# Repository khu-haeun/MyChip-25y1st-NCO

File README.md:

# My Chip Service 25y1st: **12-bit CORDIC-based NCO**

## Notice: What is **My Chip Service**?
An initiative in South Korea that provides MPW (Multi-Project Wafer) services using public fabrication facilities (fabs) for undergraduate and graduate students.
* **Official Website:** [https://www.moafab.kr](https://www.moafab.kr/css/myPage/bussiness/myChip/info)
* **Design Kit (Open-Source):** [ETRI 0.5um CMOS MPW Standard Cell DK](https://github.com/GoodKook/ETRI-0.5um-CMOS-MPW-Std-Cell-DK/tree/main)

---

## Project: 12-bit CORDIC-based NCO

### 1. Overview

*Fig 1. System Architecture*

*Fig 2. NCO implemented on a PCB using 'My Chip'*

* **Description:** A **Numerically Controlled Oscillator (NCO)** is a digital circuit that generates synchronous, discrete-time, discrete-valued representations of sinusoidal waveforms. This project implements an NCO using a **CORDIC (Coordinate Rotation Digital Computer)** array processor to calculate trigonometric values. The complete verification environment and system structure are illustrated in **Fig 1**.

* **Key Challenges: Overcoming Physical Constraints**
    * **Core Limits:** Since the NCO design exceeded the single-chip area limit, it was **partitioned into three sub-circuits** as shown in **Fig 2**:
        1. **Phase Accumulator:** Generates the phase angle.
        2. **CORDIC Processing Element:** Performs the vector rotation.
        3. **Output Terminal:** Manages the final data output, including quadrant restoration.
    * **Pad Limits:** Each chip is limited to **28 pins**. the I/O for each sub-circuit was implemented using a **2-bit serial interface**.

---

### 2. Directory Structure
```text
├── 0_Algorithm (Algorithm development, including output plots and verification)
│   ├── c_untimed: C-based NCO algorithm
│   ├── cpp_untimed: C++ based NCO algorithm
│   └── sc_timed: SystemC-based NCO model (Clock-event-based cycle-accurate design)
|
├── 1_Parallel_IO (Reference design using parallel I/O (Not implemented in this version))
|
├── 2_Splited_IO (RTL-to-GDS with Open-Source Design Kit, including output plots and verification)
│   ├── 2_0_Top_NCO: Integrated NCO system comprising all three sub-circuits
│   ├── 2_1_Phase_Acc: Sub-circuit 1
│   ├── 2_2_Cordic_Element: Sub-circuit 2
│   ├── 2_3_Output_Terminal: Sub-circuit 3
|
└── 3_Application (application cases)
    ├── 3_0_Generate_Sinusoid: Sinusoidal waveform generation
    ├── 3_1_QPSK_Communication_prototype: QPSK simulation for the prototype board
    └── 3_2_QPSK_Communication_pcb: QPSK simulation for the final PCB

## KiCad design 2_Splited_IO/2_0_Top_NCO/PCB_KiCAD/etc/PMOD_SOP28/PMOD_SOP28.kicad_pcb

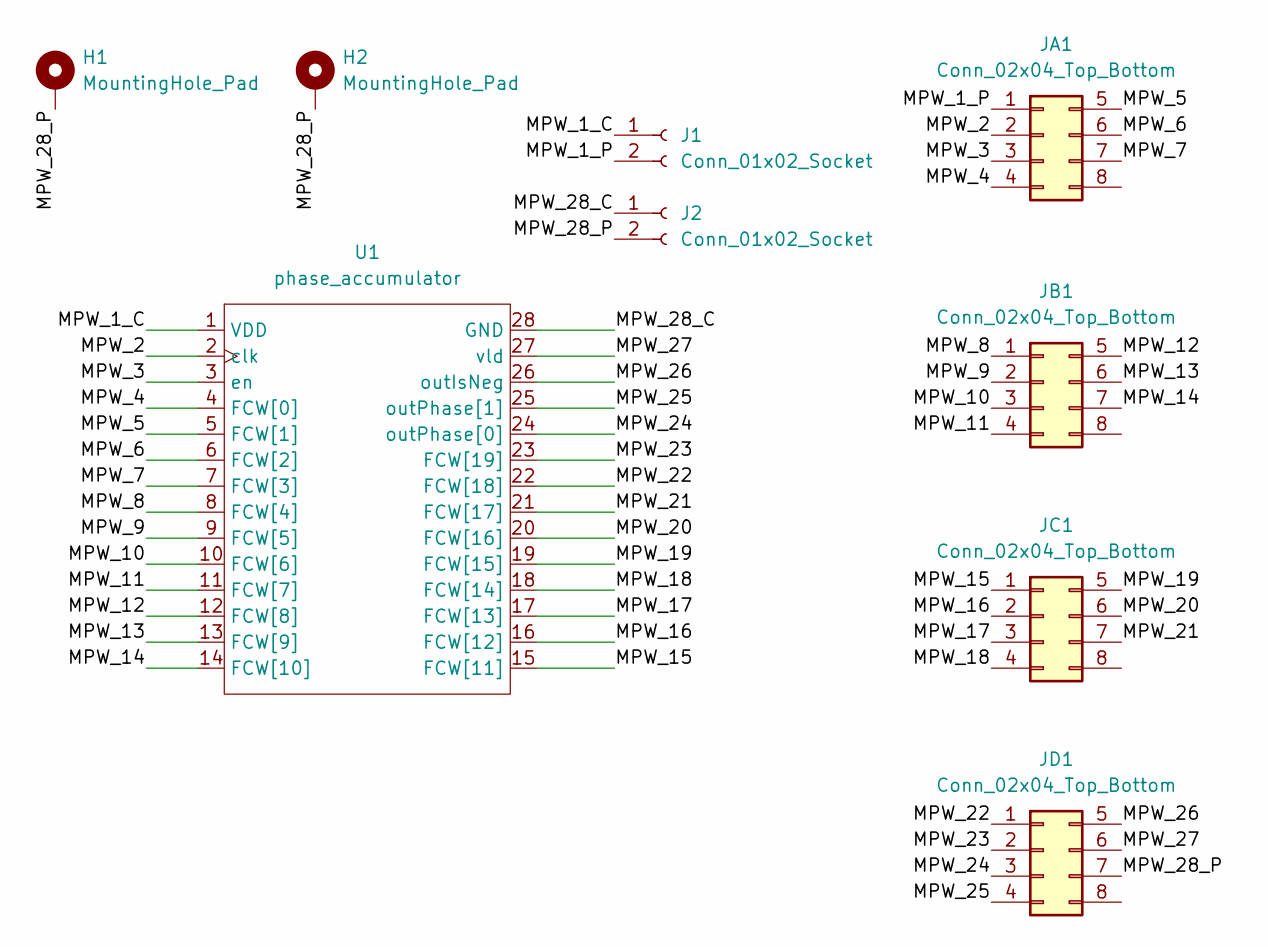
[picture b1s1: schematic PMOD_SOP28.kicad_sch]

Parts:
H1, H2: MountingHole_Pad; MountingHole_3.2mm_M3_Pad
J1, J2: Conn_01x02_Socket; PinHeader_1x02_P2.54mm_Vertical
JA1: Conn_02x04_Top_Bottom; PinSocket_2x04_P2.54mm_Vertical
JB1: Conn_02x04_Top_Bottom; PinSocket_2x04_P2.54mm_Vertical
JC1: Conn_02x04_Top_Bottom; PinSocket_2x04_P2.54mm_Vertical
JD1: Conn_02x04_Top_Bottom; PinSocket_2x04_P2.54mm_Vertical
U1: phase_accumulator; user_socket28_2p54

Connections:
/MPW_1_C: J1.1, U1.1 (VDD)
/MPW_1_P: J1.2, JA1.1
/MPW_2: JA1.2, U1.2 (clk)
/MPW_3: JA1.3, U1.3 (en)
/MPW_4: JA1.4, U1.4 (FCW[0])
/MPW_5: JA1.5, U1.5 (FCW[1])
/MPW_6: JA1.6, U1.6 (FCW[2])
/MPW_7: JA1.7, U1.7 (FCW[3])
/MPW_8: JB1.1, U1.8 (FCW[4])
/MPW_9: JB1.2, U1.9 (FCW[5])
/MPW_10: JB1.3, U1.10 (FCW[6])
/MPW_11: JB1.4, U1.11 (FCW[7])
/MPW_12: JB1.5, U1.12 (FCW[8])
/MPW_13: JB1.6, U1.13 (FCW[9])
/MPW_14: JB1.7, U1.14 (FCW[10])
/MPW_15: JC1.1, U1.15 (FCW[11])
/MPW_16: JC1.2, U1.16 (FCW[12])
/MPW_17: JC1.3, U1.17 (FCW[13])
/MPW_18: JC1.4, U1.18 (FCW[14])
/MPW_19: JC1.5, U1.19 (FCW[15])
/MPW_20: JC1.6, U1.20 (FCW[16])
/MPW_21: JC1.7, U1.21 (FCW[17])
/MPW_22: JD1.1, U1.22 (FCW[18])
/MPW_23: JD1.2, U1.23 (FCW[19])
/MPW_24: JD1.3, U1.24 (outPhase[0])
/MPW_25: JD1.4, U1.25 (outPhase[1])
/MPW_26: JD1.5, U1.26 (outIsNeg)
/MPW_27: JD1.6, U1.27 (vld)
/MPW_28_C: J2.1, U1.28 (GND)
/MPW_28_P: H1.1, H2.1, J2.2, JD1.7

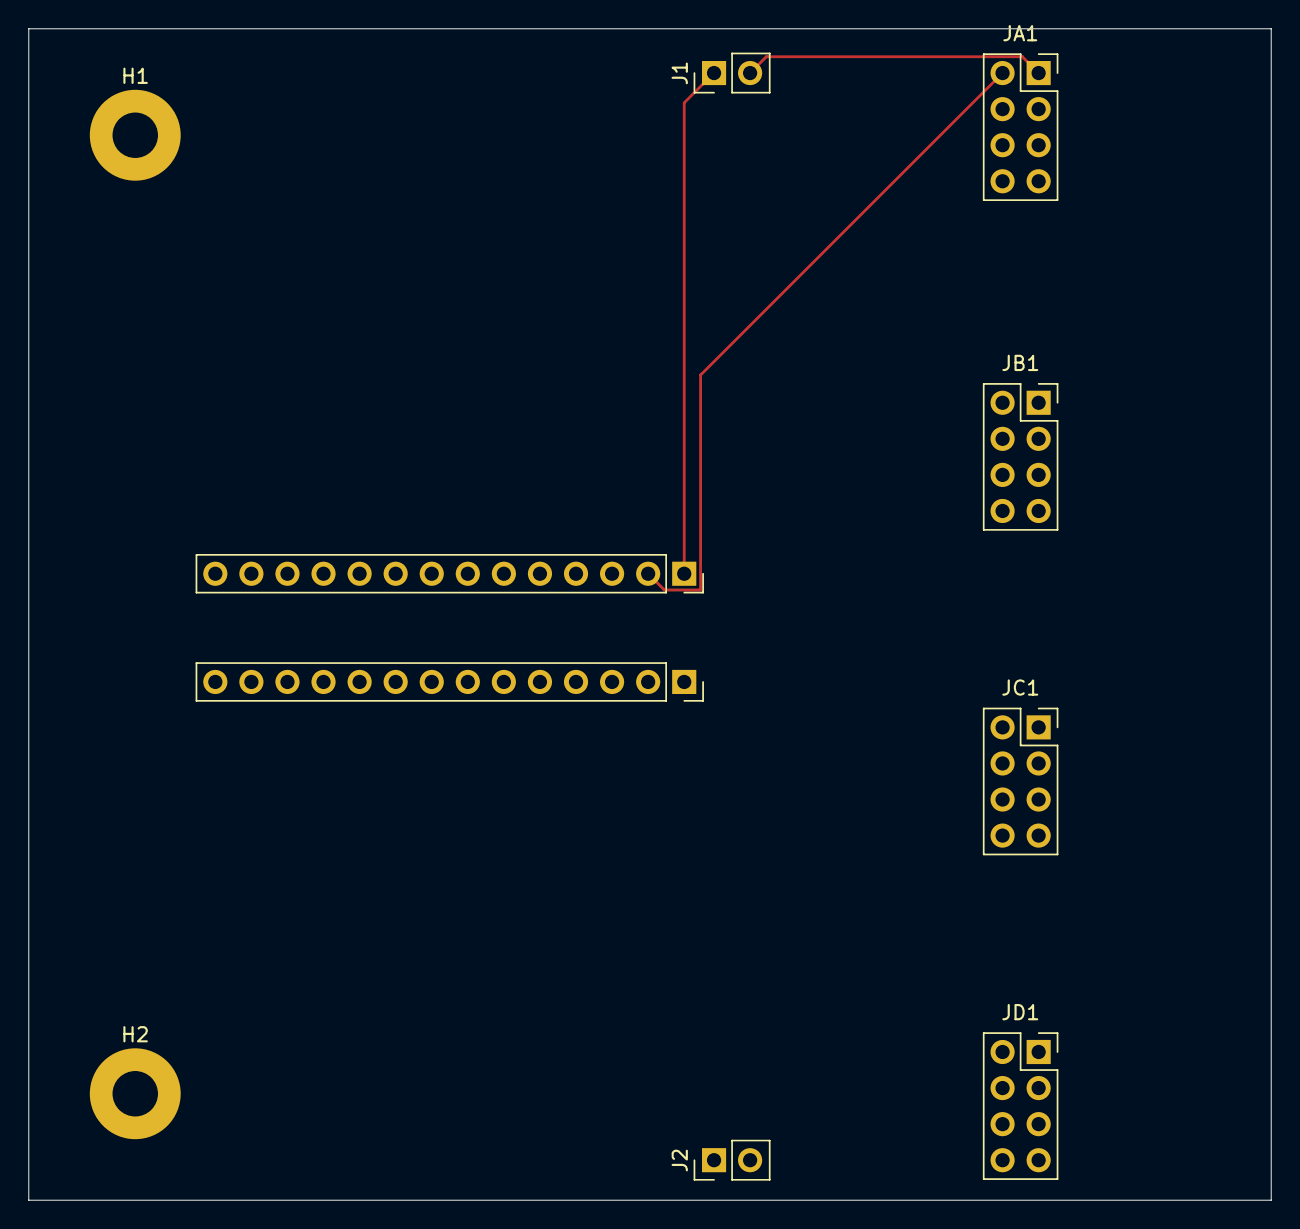
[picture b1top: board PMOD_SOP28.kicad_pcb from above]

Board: 2 copper layers, 87.5 x 82.5 mm, 9 parts (0 on the bottom side), 30 nets.

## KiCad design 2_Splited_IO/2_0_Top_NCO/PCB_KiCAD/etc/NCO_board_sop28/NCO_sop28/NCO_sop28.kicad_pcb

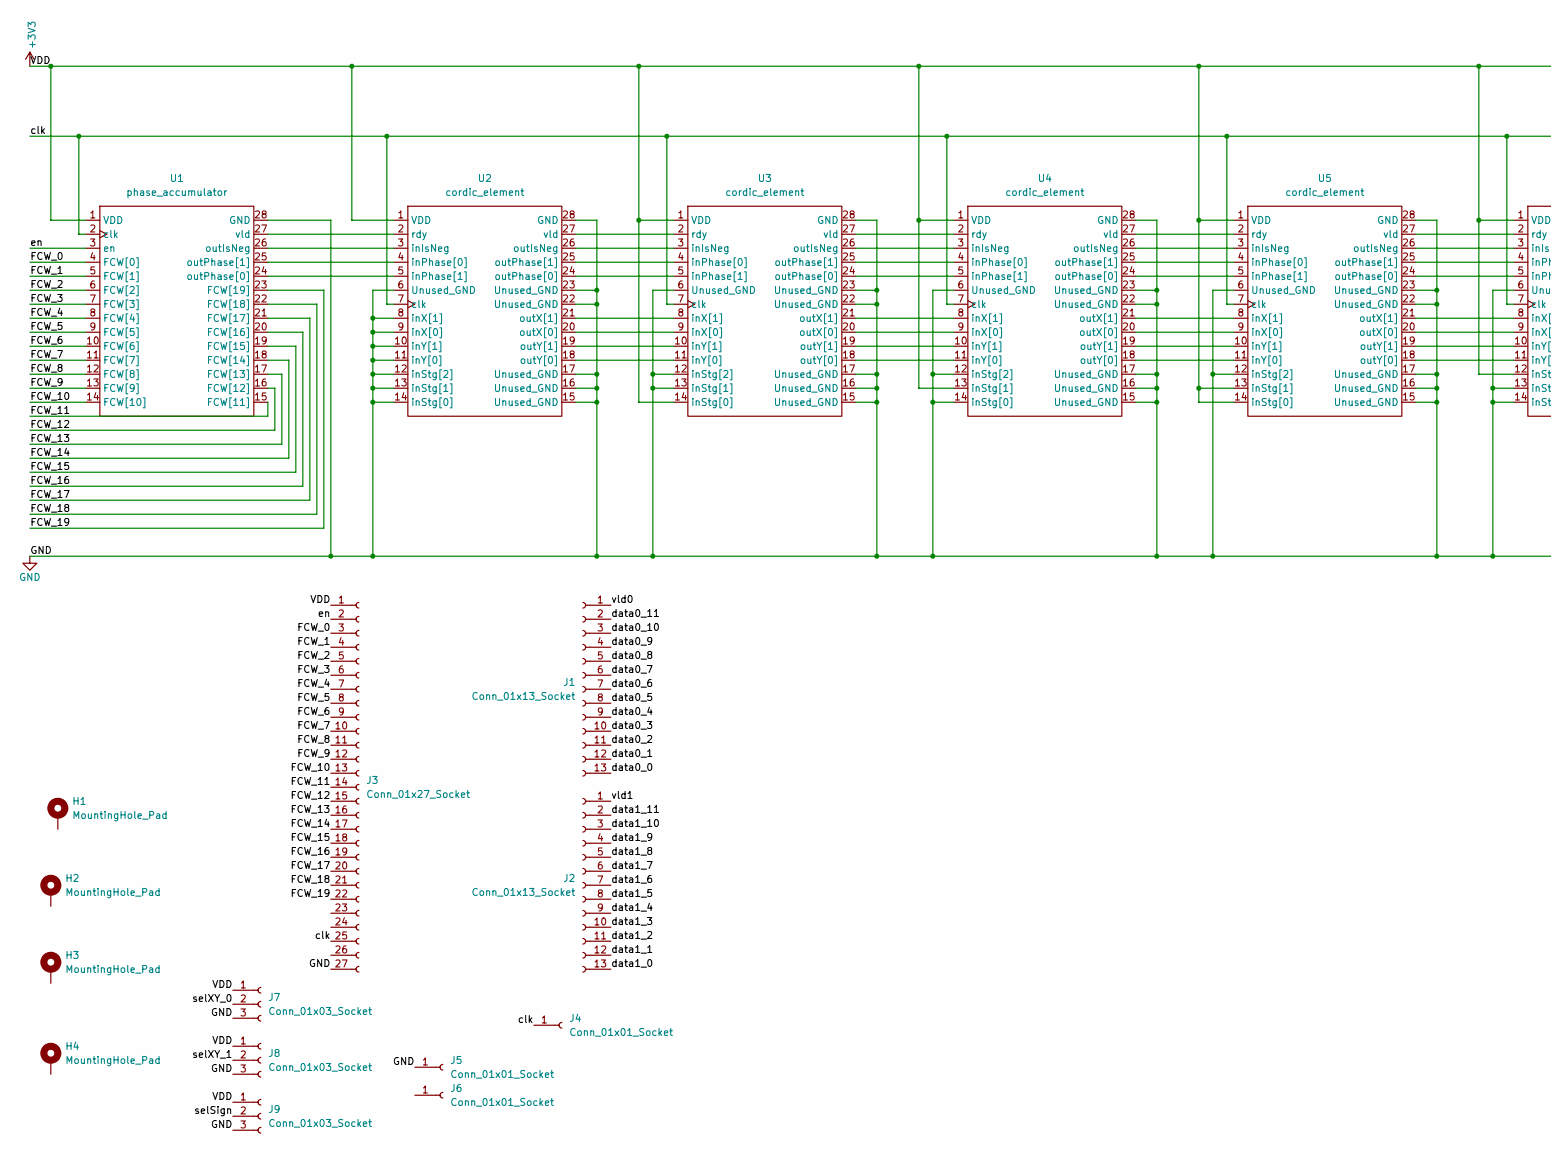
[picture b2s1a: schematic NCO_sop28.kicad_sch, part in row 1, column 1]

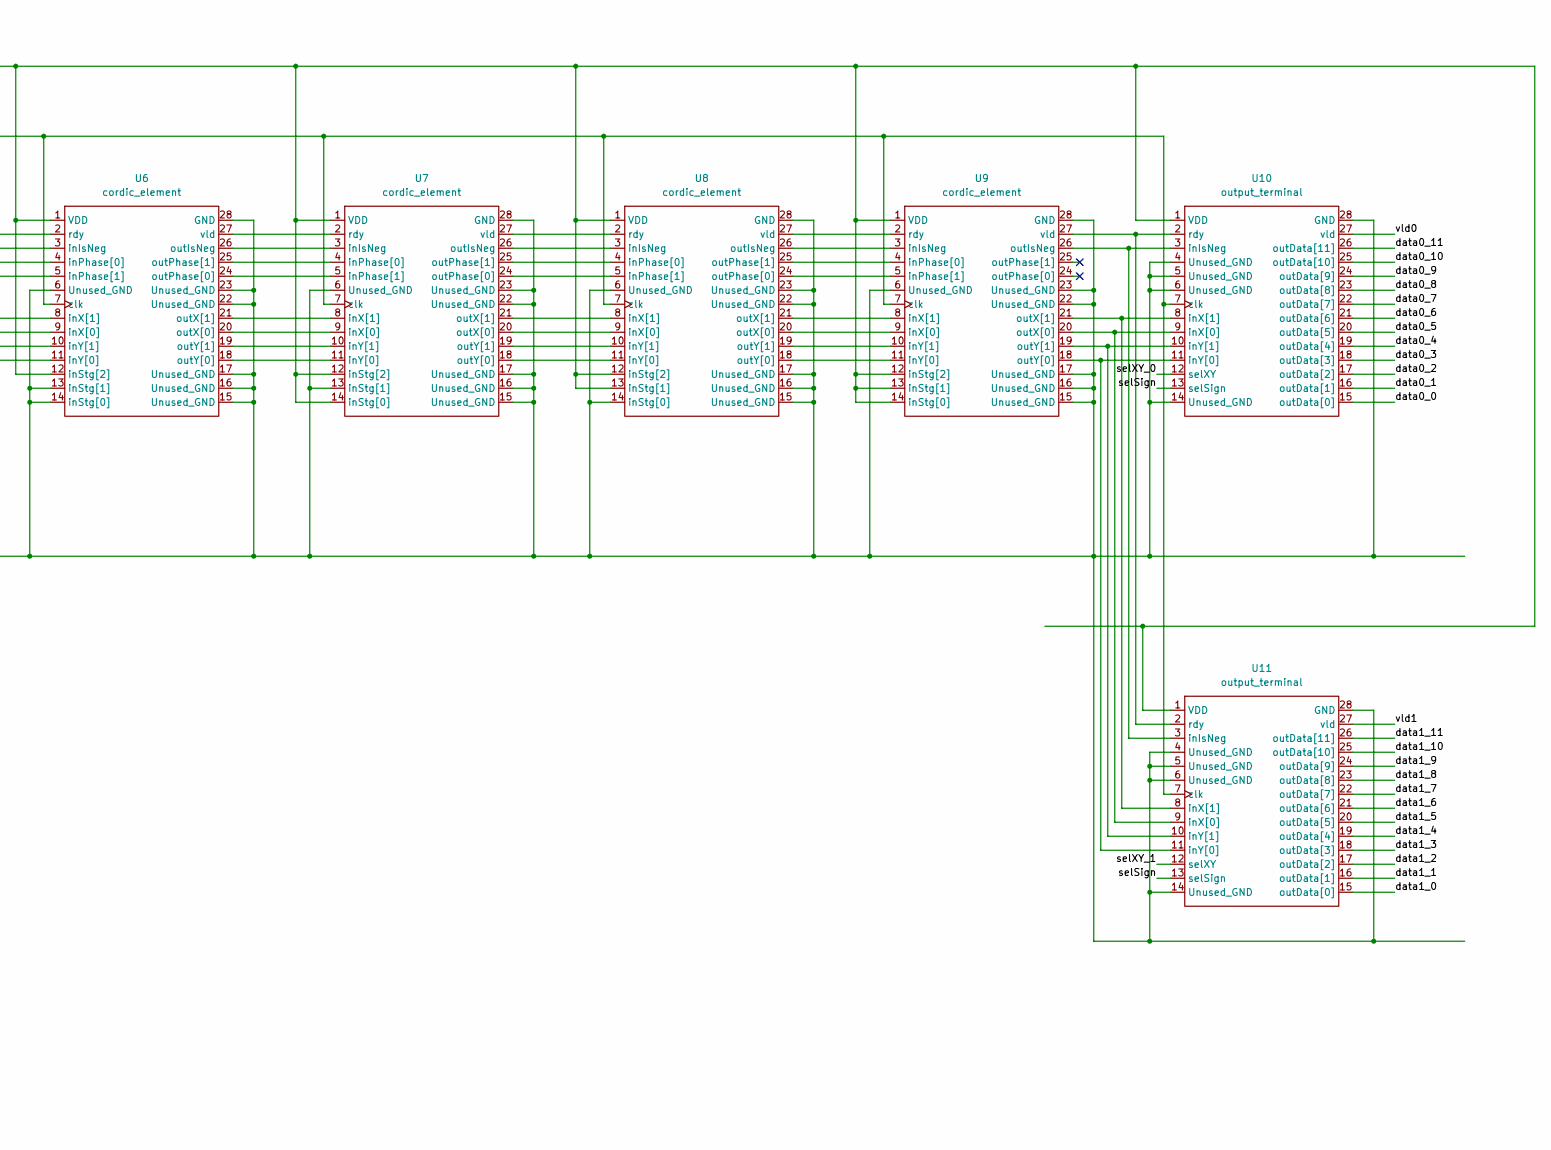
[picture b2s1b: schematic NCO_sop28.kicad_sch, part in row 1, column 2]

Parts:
H1, H2, H3, H4: MountingHole_Pad; MountingHole_3.2mm_M3_Pad
J1, J2: Conn_01x13_Socket; PinHeader_1x13_P2.54mm_Vertical
J3: Conn_01x27_Socket; PinHeader_1x27_P2.54mm_Vertical
J4, J5, J6: Conn_01x01_Socket; PinHeader_1x01_P2.54mm_Vertical
J7, J8, J9: Conn_01x03_Socket; PinHeader_1x03_P2.54mm_Vertical
U1: phase_accumulator; user_socket28_2p54
U2, U3, U4, U5, U6, U7, U8, U9: cordic_element; user_socket28_2p54
U10, U11: output_terminal; user_socket28_2p54

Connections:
+3V3: J3.1, J7.1, J8.1, J9.1, U1.1 (VDD), U2.1 (VDD), U3.1 (VDD), U3.14 (inStg[0]), U4.1 (VDD), U4.13 (inStg[1]), U5.1 (VDD), U5.13 (inStg[1]), U5.14 (inStg[0]), U6.1 (VDD), U6.12 (inStg[2]), U7.1 (VDD), U7.12 (inStg[2]), U7.14 (inStg[0]), U8.1 (VDD), U8.12 (inStg[2]), U8.13 (inStg[1]), U9.1 (VDD), U9.12 (inStg[2]), U9.13 (inStg[1]), U9.14 (inStg[0]), U10.1 (VDD), U11.1 (VDD)
/FCW_0: J3.3, U1.4 (FCW[0])
/FCW_1: J3.4, U1.5 (FCW[1])
/FCW_2: J3.5, U1.6 (FCW[2])
/FCW_3: J3.6, U1.7 (FCW[3])
/FCW_4: J3.7, U1.8 (FCW[4])
/FCW_5: J3.8, U1.9 (FCW[5])
/FCW_6: J3.9, U1.10 (FCW[6])
/FCW_7: J3.10, U1.11 (FCW[7])
/FCW_8: J3.11, U1.12 (FCW[8])
/FCW_9: J3.12, U1.13 (FCW[9])
/FCW_10: J3.13, U1.14 (FCW[10])
/FCW_11: J3.14, U1.15 (FCW[11])
/FCW_12: J3.15, U1.16 (FCW[12])
/FCW_13: J3.16, U1.17 (FCW[13])
/FCW_14: J3.17, U1.18 (FCW[14])
/FCW_15: J3.18, U1.19 (FCW[15])
/FCW_16: J3.19, U1.20 (FCW[16])
/FCW_17: J3.20, U1.21 (FCW[17])
/FCW_18: J3.21, U1.22 (FCW[18])
/FCW_19: J3.22, U1.23 (FCW[19])
/clk: J3.25, J4.1, U1.2 (clk), U2.7 (clk), U3.7 (clk), U4.7 (clk), U5.7 (clk), U6.7 (clk), U7.7 (clk), U8.7 (clk), U9.7 (clk), U10.7 (clk), U11.7 (clk)
/data0_0: J1.13, U10.15 (outData[0])
/data0_1: J1.12, U10.16 (outData[1])
/data0_2: J1.11, U10.17 (outData[2])
/data0_3: J1.10, U10.18 (outData[3])
/data0_4: J1.9, U10.19 (outData[4])
/data0_5: J1.8, U10.20 (outData[5])
/data0_6: J1.7, U10.21 (outData[6])
/data0_7: J1.6, U10.22 (outData[7])
/data0_8: J1.5, U10.23 (outData[8])
/data0_9: J1.4, U10.24 (outData[9])
/data0_10: J1.3, U10.25 (outData[10])
/data0_11: J1.2, U10.26 (outData[11])
/data1_0: J2.13, U11.15 (outData[0])
/data1_1: J2.12, U11.16 (outData[1])
/data1_2: J2.11, U11.17 (outData[2])
/data1_3: J2.10, U11.18 (outData[3])
/data1_4: J2.9, U11.19 (outData[4])
/data1_5: J2.8, U11.20 (outData[5])
/data1_6: J2.7, U11.21 (outData[6])
/data1_7: J2.6, U11.22 (outData[7])
/data1_8: J2.5, U11.23 (outData[8])
/data1_9: J2.4, U11.24 (outData[9])
/data1_10: J2.3, U11.25 (outData[10])
/data1_11: J2.2, U11.26 (outData[11])
/en: J3.2, U1.3 (en)
/selSign: J9.2, U10.13 (selSign), U11.13 (selSign)
/selXY_0: J7.2, U10.12 (selXY)
/selXY_1: J8.2, U11.12 (selXY)
/vld0: J1.1, U10.27 (vld)
/vld1: J2.1, U11.27 (vld)
GND: J3.27, J5.1, J7.3, J8.3, J9.3, U1.28 (GND), U2.6 (Unused_GND), U2.8 (inX[1]), U2.9 (inX[0]), U2.10 (inY[1]), U2.11 (inY[0]), U2.12 (inStg[2]), U2.13 (inStg[1]), U2.14 (inStg[0]), U2.15 (Unused_GND), U2.16 (Unused_GND), U2.17 (Unused_GND), U2.22 (Unused_GND), U2.23 (Unused_GND), U2.28 (GND), U3.6 (Unused_GND), U3.12 (inStg[2]), U3.13 (inStg[1]), U3.15 (Unused_GND), U3.16 (Unused_GND), U3.17 (Unused_GND), U3.22 (Unused_GND), U3.23 (Unused_GND), U3.28 (GND), U4.6 (Unused_GND), U4.12 (inStg[2]), U4.14 (inStg[0]), U4.15 (Unused_GND), U4.16 (Unused_GND), U4.17 (Unused_GND), U4.22 (Unused_GND), U4.23 (Unused_GND), U4.28 (GND), U5.6 (Unused_GND), U5.12 (inStg[2]), U5.15 (Unused_GND), U5.16 (Unused_GND), U5.17 (Unused_GND), U5.22 (Unused_GND), U5.23 (Unused_GND), U5.28 (GND), U6.6 (Unused_GND), U6.13 (inStg[1]), U6.14 (inStg[0]), U6.15 (Unused_GND), U6.16 (Unused_GND), U6.17 (Unused_GND), U6.22 (Unused_GND), U6.23 (Unused_GND), U6.28 (GND), U7.6 (Unused_GND), U7.13 (inStg[1]), U7.15 (Unused_GND), U7.16 (Unused_GND), U7.17 (Unused_GND), U7.22 (Unused_GND), U7.23 (Unused_GND), U7.28 (GND), U8.6 (Unused_GND), U8.14 (inStg[0]), U8.15 (Unused_GND), U8.16 (Unused_GND), U8.17 (Unused_GND), U8.22 (Unused_GND), U8.23 (Unused_GND), U8.28 (GND), U9.6 (Unused_GND), U9.15 (Unused_GND), U9.16 (Unused_GND), U9.17 (Unused_GND), U9.22 (Unused_GND), U9.23 (Unused_GND), U9.28 (GND), U10.4 (Unused_GND), U10.5 (Unused_GND), U10.6 (Unused_GND), U10.14 (Unused_GND), U10.28 (GND), U11.4 (Unused_GND), U11.5 (Unused_GND), U11.6 (Unused_GND), U11.14 (Unused_GND), U11.28 (GND)
unnamed: U1.26 (outIsNeg), U2.3 (inIsNeg)
unnamed: U1.24 (outPhase[0]), U2.5 (inPhase[1])
unnamed: U1.25 (outPhase[1]), U2.4 (inPhase[0])
unnamed: U1.27 (vld), U2.2 (rdy)
unnamed: U2.26 (outIsNeg), U3.3 (inIsNeg)
unnamed: U2.24 (outPhase[0]), U3.5 (inPhase[1])
unnamed: U2.25 (outPhase[1]), U3.4 (inPhase[0])
unnamed: U2.20 (outX[0]), U3.9 (inX[0])
unnamed: U2.21 (outX[1]), U3.8 (inX[1])
unnamed: U2.18 (outY[0]), U3.11 (inY[0])
unnamed: U2.19 (outY[1]), U3.10 (inY[1])
unnamed: U2.27 (vld), U3.2 (rdy)
unnamed: U3.26 (outIsNeg), U4.3 (inIsNeg)
unnamed: U3.24 (outPhase[0]), U4.5 (inPhase[1])
unnamed: U3.25 (outPhase[1]), U4.4 (inPhase[0])
unnamed: U3.20 (outX[0]), U4.9 (inX[0])
unnamed: U3.21 (outX[1]), U4.8 (inX[1])
unnamed: U3.18 (outY[0]), U4.11 (inY[0])
unnamed: U3.19 (outY[1]), U4.10 (inY[1])
unnamed: U3.27 (vld), U4.2 (rdy)
unnamed: U4.26 (outIsNeg), U5.3 (inIsNeg)
unnamed: U4.24 (outPhase[0]), U5.5 (inPhase[1])
unnamed: U4.25 (outPhase[1]), U5.4 (inPhase[0])
unnamed: U4.20 (outX[0]), U5.9 (inX[0])
unnamed: U4.21 (outX[1]), U5.8 (inX[1])
unnamed: U4.18 (outY[0]), U5.11 (inY[0])
unnamed: U4.19 (outY[1]), U5.10 (inY[1])
unnamed: U4.27 (vld), U5.2 (rdy)
unnamed: U5.26 (outIsNeg), U6.3 (inIsNeg)
unnamed: U5.24 (outPhase[0]), U6.5 (inPhase[1])
unnamed: U5.25 (outPhase[1]), U6.4 (inPhase[0])
unnamed: U5.20 (outX[0]), U6.9 (inX[0])
unnamed: U5.21 (outX[1]), U6.8 (inX[1])
unnamed: U5.18 (outY[0]), U6.11 (inY[0])
unnamed: U5.19 (outY[1]), U6.10 (inY[1])
unnamed: U5.27 (vld), U6.2 (rdy)
unnamed: U6.26 (outIsNeg), U7.3 (inIsNeg)
unnamed: U6.24 (outPhase[0]), U7.5 (inPhase[1])
unnamed: U6.25 (outPhase[1]), U7.4 (inPhase[0])
unnamed: U6.20 (outX[0]), U7.9 (inX[0])
unnamed: U6.21 (outX[1]), U7.8 (inX[1])
unnamed: U6.18 (outY[0]), U7.11 (inY[0])
unnamed: U6.19 (outY[1]), U7.10 (inY[1])
unnamed: U6.27 (vld), U7.2 (rdy)
unnamed: U7.26 (outIsNeg), U8.3 (inIsNeg)
unnamed: U7.24 (outPhase[0]), U8.5 (inPhase[1])
unnamed: U7.25 (outPhase[1]), U8.4 (inPhase[0])
unnamed: U7.20 (outX[0]), U8.9 (inX[0])
unnamed: U7.21 (outX[1]), U8.8 (inX[1])
unnamed: U7.18 (outY[0]), U8.11 (inY[0])
unnamed: U7.19 (outY[1]), U8.10 (inY[1])
unnamed: U7.27 (vld), U8.2 (rdy)
unnamed: U8.26 (outIsNeg), U9.3 (inIsNeg)
unnamed: U8.24 (outPhase[0]), U9.5 (inPhase[1])
unnamed: U8.25 (outPhase[1]), U9.4 (inPhase[0])
unnamed: U8.20 (outX[0]), U9.9 (inX[0])
unnamed: U8.21 (outX[1]), U9.8 (inX[1])
unnamed: U8.18 (outY[0]), U9.11 (inY[0])
unnamed: U8.19 (outY[1]), U9.10 (inY[1])
unnamed: U8.27 (vld), U9.2 (rdy)
unnamed: U9.26 (outIsNeg), U10.3 (inIsNeg), U11.3 (inIsNeg)
unnamed: U9.20 (outX[0]), U10.9 (inX[0]), U11.9 (inX[0])
unnamed: U9.21 (outX[1]), U10.8 (inX[1]), U11.8 (inX[1])
unnamed: U9.18 (outY[0]), U10.11 (inY[0]), U11.11 (inY[0])
unnamed: U9.19 (outY[1]), U10.10 (inY[1]), U11.10 (inY[1])
unnamed: U9.27 (vld), U10.2 (rdy), U11.2 (rdy)

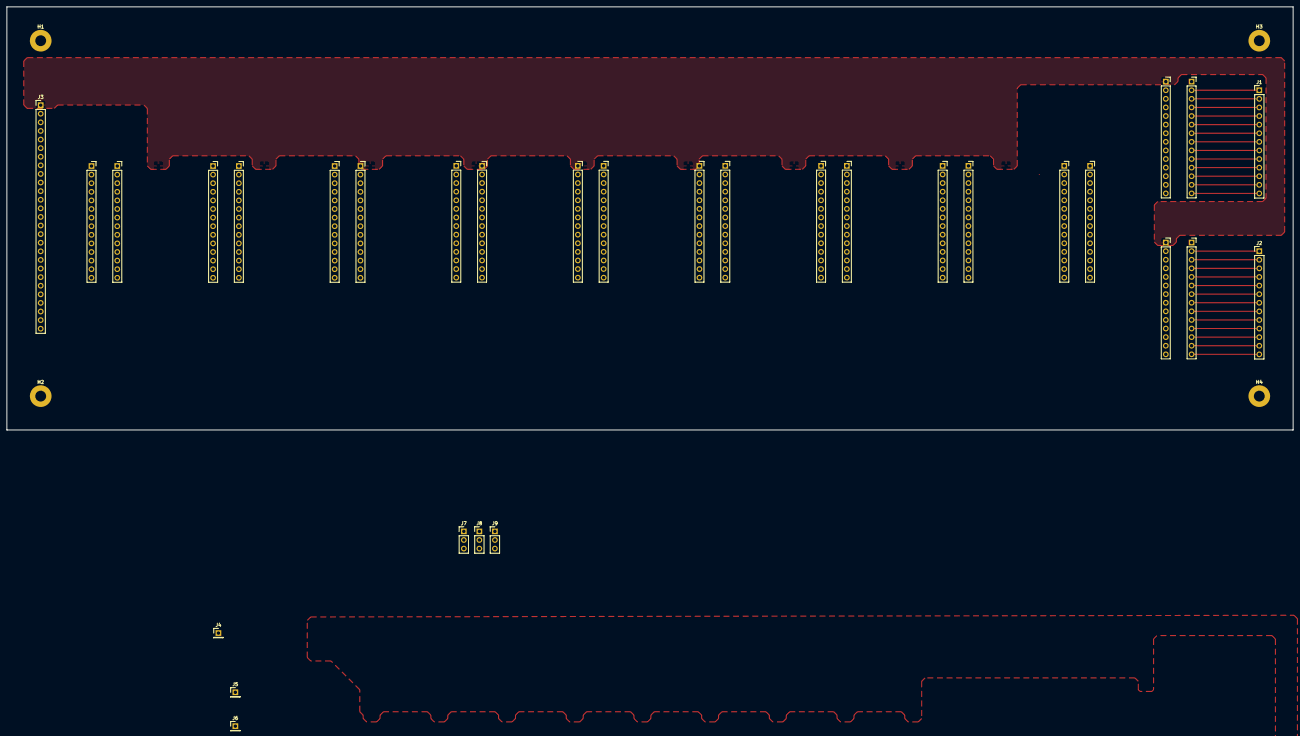
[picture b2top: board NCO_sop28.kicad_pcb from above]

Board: 2 copper layers, 380.0 x 125.0 mm, 24 parts (0 on the bottom side), 119 nets.

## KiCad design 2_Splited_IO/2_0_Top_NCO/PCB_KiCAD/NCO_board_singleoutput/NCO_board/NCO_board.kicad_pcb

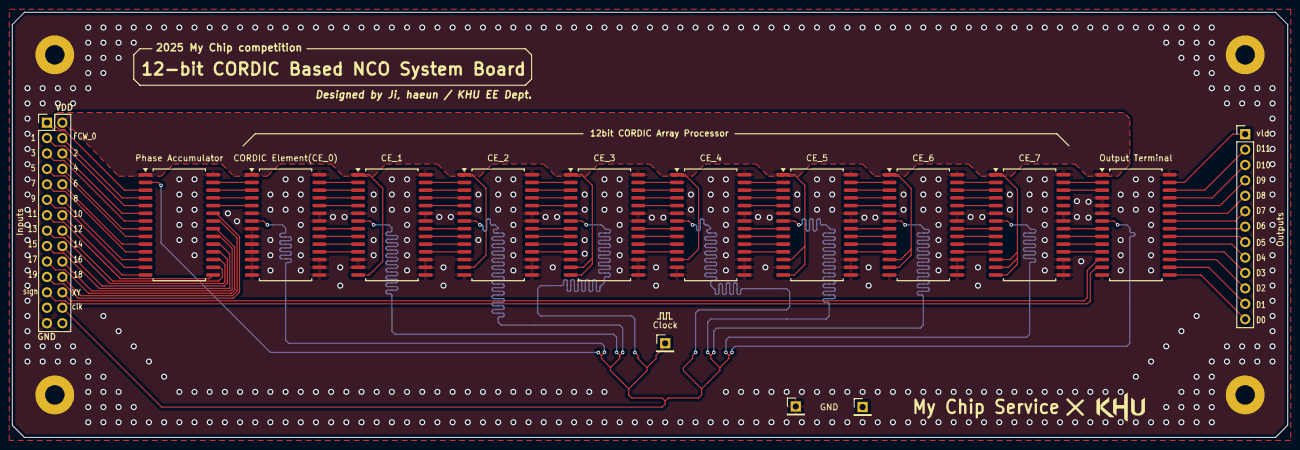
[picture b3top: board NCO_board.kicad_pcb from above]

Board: 2 copper layers, 210.0 x 70.0 mm, 19 parts (0 on the bottom side), 105 nets.

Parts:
CE_1, CE_2, CE_3, CE_4, CE_5, CE_6, CE_7: cordic_element; SOP-28_8.4x18.16mm_P1.27mm
CORDIC Element(CE_0): cordic_element; SOP-28_8.4x18.16mm_P1.27mm
Clock: Conn_01x01_Socket; PinHeader_1x01_P2.54mm_Vertical
GND: Conn_01x01_Socket; PinHeader_1x01_P2.54mm_Vertical
H1, H2, H3, H4: MountingHole_Pad; MountingHole_3.2mm_M3_Pad
Inputs: Conn_02x14_Odd_Even; PinHeader_2x14_P2.54mm_Vertical
J6: Conn_01x01_Socket; PinHeader_1x01_P2.54mm_Vertical
Output Terminal: output_terminal; SOP-28_8.4x18.16mm_P1.27mm
Outputs: Conn_01x13_Socket; PinHeader_1x13_P2.54mm_Vertical
Phase Accumulator: phase_accumulator; SOP-28_8.4x18.16mm_P1.27mm

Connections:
+3V3: CE_1.1 (VDD), CE_1.14 (inStg[0]), CE_2.1 (VDD), CE_2.13 (inStg[1]), CE_3.1 (VDD), CE_3.13 (inStg[1]), CE_3.14 (inStg[0]), CE_4.1 (VDD), CE_4.12 (inStg[2]), CE_5.1 (VDD), CE_5.12 (inStg[2]), CE_5.14 (inStg[0]), CE_6.1 (VDD), CE_6.12 (inStg[2]), CE_6.13 (inStg[1]), CE_7.1 (VDD), CE_7.12 (inStg[2]), CE_7.13 (inStg[1]), CE_7.14 (inStg[0]), CORDIC Element(CE_0).1 (VDD), Inputs.2, Output Terminal.1 (VDD), Phase Accumulator.1 (VDD)
/FCW_0: Inputs.4, Phase Accumulator.4 (FCW[0])
/FCW_1: Inputs.3, Phase Accumulator.5 (FCW[1])
/FCW_2: Inputs.6, Phase Accumulator.6 (FCW[2])
/FCW_3: Inputs.5, Phase Accumulator.7 (FCW[3])
/FCW_4: Inputs.8, Phase Accumulator.8 (FCW[4])
/FCW_5: Inputs.7, Phase Accumulator.9 (FCW[5])
/FCW_6: Inputs.10, Phase Accumulator.10 (FCW[6])
/FCW_7: Inputs.9, Phase Accumulator.11 (FCW[7])
/FCW_8: Inputs.12, Phase Accumulator.12 (FCW[8])
/FCW_9: Inputs.11, Phase Accumulator.13 (FCW[9])
/FCW_10: Inputs.14, Phase Accumulator.14 (FCW[10])
/FCW_11: Inputs.13, Phase Accumulator.15 (FCW[11])
/FCW_12: Inputs.16, Phase Accumulator.16 (FCW[12])
/FCW_13: Inputs.15, Phase Accumulator.17 (FCW[13])
/FCW_14: Inputs.18, Phase Accumulator.18 (FCW[14])
/FCW_15: Inputs.17, Phase Accumulator.19 (FCW[15])
/FCW_16: Inputs.20, Phase Accumulator.20 (FCW[16])
/FCW_17: Inputs.19, Phase Accumulator.21 (FCW[17])
/FCW_18: Inputs.22, Phase Accumulator.22 (FCW[18])
/FCW_19: Inputs.21, Phase Accumulator.23 (FCW[19])
/clk: CE_1.7 (clk), CE_2.7 (clk), CE_3.7 (clk), CE_4.7 (clk), CE_5.7 (clk), CE_6.7 (clk), CE_7.7 (clk), CORDIC Element(CE_0).7 (clk), Clock.1, Inputs.26, Output Terminal.7 (clk), Phase Accumulator.2 (clk)
/data_0: Output Terminal.15 (outData[0]), Outputs.13
/data_1: Output Terminal.16 (outData[1]), Outputs.12
/data_2: Output Terminal.17 (outData[2]), Outputs.11
/data_3: Output Terminal.18 (outData[3]), Outputs.10
/data_4: Output Terminal.19 (outData[4]), Outputs.9
/data_5: Output Terminal.20 (outData[5]), Outputs.8
/data_6: Output Terminal.21 (outData[6]), Outputs.7
/data_7: Output Terminal.22 (outData[7]), Outputs.6
/data_8: Output Terminal.23 (outData[8]), Outputs.5
/data_9: Output Terminal.24 (outData[9]), Outputs.4
/data_10: Output Terminal.25 (outData[10]), Outputs.3
/data_11: Output Terminal.26 (outData[11]), Outputs.2
/en: Inputs.1, Phase Accumulator.3 (en)
/selSign: Inputs.23, Output Terminal.13 (selSign)
/selXY: Inputs.24, Output Terminal.12 (selXY)
/vld: Output Terminal.27 (vld), Outputs.1
GND: CE_1.6 (Unused_GND), CE_1.12 (inStg[2]), CE_1.13 (inStg[1]), CE_1.15 (Unused_GND), CE_1.16 (Unused_GND), CE_1.17 (Unused_GND), CE_1.22 (Unused_GND), CE_1.23 (Unused_GND), CE_1.28 (GND), CE_2.6 (Unused_GND), CE_2.12 (inStg[2]), CE_2.14 (inStg[0]), CE_2.15 (Unused_GND), CE_2.16 (Unused_GND), CE_2.17 (Unused_GND), CE_2.22 (Unused_GND), CE_2.23 (Unused_GND), CE_2.28 (GND), CE_3.6 (Unused_GND), CE_3.12 (inStg[2]), CE_3.15 (Unused_GND), CE_3.16 (Unused_GND), CE_3.17 (Unused_GND), CE_3.22 (Unused_GND), CE_3.23 (Unused_GND), CE_3.28 (GND), CE_4.6 (Unused_GND), CE_4.13 (inStg[1]), CE_4.14 (inStg[0]), CE_4.15 (Unused_GND), CE_4.16 (Unused_GND), CE_4.17 (Unused_GND), CE_4.22 (Unused_GND), CE_4.23 (Unused_GND), CE_4.28 (GND), CE_5.6 (Unused_GND), CE_5.13 (inStg[1]), CE_5.15 (Unused_GND), CE_5.16 (Unused_GND), CE_5.17 (Unused_GND), CE_5.22 (Unused_GND), CE_5.23 (Unused_GND), CE_5.28 (GND), CE_6.6 (Unused_GND), CE_6.14 (inStg[0]), CE_6.15 (Unused_GND), CE_6.16 (Unused_GND), CE_6.17 (Unused_GND), CE_6.22 (Unused_GND), CE_6.23 (Unused_GND), CE_6.28 (GND), CE_7.6 (Unused_GND), CE_7.15 (Unused_GND), CE_7.16 (Unused_GND), CE_7.17 (Unused_GND), CE_7.22 (Unused_GND), CE_7.23 (Unused_GND), CE_7.28 (GND), CORDIC Element(CE_0).6 (Unused_GND), CORDIC Element(CE_0).8 (inX[1]), CORDIC Element(CE_0).9 (inX[0]), CORDIC Element(CE_0).10 (inY[1]), CORDIC Element(CE_0).11 (inY[0]), CORDIC Element(CE_0).12 (inStg[2]), CORDIC Element(CE_0).13 (inStg[1]), CORDIC Element(CE_0).14 (inStg[0]), CORDIC Element(CE_0).15 (Unused_GND), CORDIC Element(CE_0).16 (Unused_GND), CORDIC Element(CE_0).17 (Unused_GND), CORDIC Element(CE_0).22 (Unused_GND), CORDIC Element(CE_0).23 (Unused_GND), CORDIC Element(CE_0).28 (GND), GND.1, H1.1, H2.1, H3.1, H4.1, Inputs.27, Output Terminal.4 (Unused_GND), Output Terminal.5 (Unused_GND), Output Terminal.6 (Unused_GND), Output Terminal.14 (Unused_GND), Output Terminal.28 (GND), Phase Accumulator.28 (GND)
unnamed: CORDIC Element(CE_0).3 (inIsNeg), Phase Accumulator.26 (outIsNeg)
unnamed: CORDIC Element(CE_0).5 (inPhase[1]), Phase Accumulator.24 (outPhase[0])
unnamed: CORDIC Element(CE_0).4 (inPhase[0]), Phase Accumulator.25 (outPhase[1])
unnamed: CORDIC Element(CE_0).2 (rdy), Phase Accumulator.27 (vld)
unnamed: CE_1.3 (inIsNeg), CORDIC Element(CE_0).26 (outIsNeg)
unnamed: CE_1.5 (inPhase[1]), CORDIC Element(CE_0).24 (outPhase[0])
unnamed: CE_1.4 (inPhase[0]), CORDIC Element(CE_0).25 (outPhase[1])
unnamed: CE_1.9 (inX[0]), CORDIC Element(CE_0).20 (outX[0])
unnamed: CE_1.8 (inX[1]), CORDIC Element(CE_0).21 (outX[1])
unnamed: CE_1.11 (inY[0]), CORDIC Element(CE_0).18 (outY[0])
unnamed: CE_1.10 (inY[1]), CORDIC Element(CE_0).19 (outY[1])
unnamed: CE_1.2 (rdy), CORDIC Element(CE_0).27 (vld)
unnamed: CE_1.26 (outIsNeg), CE_2.3 (inIsNeg)
unnamed: CE_1.24 (outPhase[0]), CE_2.5 (inPhase[1])
unnamed: CE_1.25 (outPhase[1]), CE_2.4 (inPhase[0])
unnamed: CE_1.20 (outX[0]), CE_2.9 (inX[0])
unnamed: CE_1.21 (outX[1]), CE_2.8 (inX[1])
unnamed: CE_1.18 (outY[0]), CE_2.11 (inY[0])
unnamed: CE_1.19 (outY[1]), CE_2.10 (inY[1])
unnamed: CE_1.27 (vld), CE_2.2 (rdy)
unnamed: CE_2.26 (outIsNeg), CE_3.3 (inIsNeg)
unnamed: CE_2.24 (outPhase[0]), CE_3.5 (inPhase[1])
unnamed: CE_2.25 (outPhase[1]), CE_3.4 (inPhase[0])
unnamed: CE_2.20 (outX[0]), CE_3.9 (inX[0])
unnamed: CE_2.21 (outX[1]), CE_3.8 (inX[1])
unnamed: CE_2.18 (outY[0]), CE_3.11 (inY[0])
unnamed: CE_2.19 (outY[1]), CE_3.10 (inY[1])
unnamed: CE_2.27 (vld), CE_3.2 (rdy)
unnamed: CE_3.26 (outIsNeg), CE_4.3 (inIsNeg)
unnamed: CE_3.24 (outPhase[0]), CE_4.5 (inPhase[1])
unnamed: CE_3.25 (outPhase[1]), CE_4.4 (inPhase[0])
unnamed: CE_3.20 (outX[0]), CE_4.9 (inX[0])
unnamed: CE_3.21 (outX[1]), CE_4.8 (inX[1])
unnamed: CE_3.18 (outY[0]), CE_4.11 (inY[0])
unnamed: CE_3.19 (outY[1]), CE_4.10 (inY[1])
unnamed: CE_3.27 (vld), CE_4.2 (rdy)
unnamed: CE_4.26 (outIsNeg), CE_5.3 (inIsNeg)
unnamed: CE_4.24 (outPhase[0]), CE_5.5 (inPhase[1])
unnamed: CE_4.25 (outPhase[1]), CE_5.4 (inPhase[0])
unnamed: CE_4.20 (outX[0]), CE_5.9 (inX[0])
unnamed: CE_4.21 (outX[1]), CE_5.8 (inX[1])
unnamed: CE_4.18 (outY[0]), CE_5.11 (inY[0])
unnamed: CE_4.19 (outY[1]), CE_5.10 (inY[1])
unnamed: CE_4.27 (vld), CE_5.2 (rdy)
unnamed: CE_5.26 (outIsNeg), CE_6.3 (inIsNeg)
unnamed: CE_5.24 (outPhase[0]), CE_6.5 (inPhase[1])
unnamed: CE_5.25 (outPhase[1]), CE_6.4 (inPhase[0])
unnamed: CE_5.20 (outX[0]), CE_6.9 (inX[0])
unnamed: CE_5.21 (outX[1]), CE_6.8 (inX[1])
unnamed: CE_5.18 (outY[0]), CE_6.11 (inY[0])
unnamed: CE_5.19 (outY[1]), CE_6.10 (inY[1])
unnamed: CE_5.27 (vld), CE_6.2 (rdy)
unnamed: CE_6.26 (outIsNeg), CE_7.3 (inIsNeg)
unnamed: CE_6.24 (outPhase[0]), CE_7.5 (inPhase[1])
unnamed: CE_6.25 (outPhase[1]), CE_7.4 (inPhase[0])
unnamed: CE_6.20 (outX[0]), CE_7.9 (inX[0])
unnamed: CE_6.21 (outX[1]), CE_7.8 (inX[1])
unnamed: CE_6.18 (outY[0]), CE_7.11 (inY[0])
unnamed: CE_6.19 (outY[1]), CE_7.10 (inY[1])
unnamed: CE_6.27 (vld), CE_7.2 (rdy)
unnamed: CE_7.26 (outIsNeg), Output Terminal.3 (inIsNeg)
unnamed: CE_7.20 (outX[0]), Output Terminal.9 (inX[0])
unnamed: CE_7.21 (outX[1]), Output Terminal.8 (inX[1])
unnamed: CE_7.18 (outY[0]), Output Terminal.11 (inY[0])
unnamed: CE_7.19 (outY[1]), Output Terminal.10 (inY[1])
unnamed: CE_7.27 (vld), Output Terminal.2 (rdy)

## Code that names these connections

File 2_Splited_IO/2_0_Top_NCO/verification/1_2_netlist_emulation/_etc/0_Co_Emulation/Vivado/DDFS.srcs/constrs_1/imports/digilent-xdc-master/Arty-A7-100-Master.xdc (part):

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#set_property -dict { PACKAGE_PIN T15   IOSTANDARD LVCMOS33 } [get_ports { ck_io6  }]; #IO_L14N_T2_SRCC_14 Sch=ck_io[6]
#set_property -dict { PACKAGE_PIN T16   IOSTANDARD LVCMOS33 } [get_ports { ck_io7  }]; #IO_L15N_T2_DQS_DOUT_CSO_B_14 Sch=ck_io[7]
#set_property -dict { PACKAGE_PIN N15   IOSTANDARD LVCMOS33 } [get_ports { ck_io8  }]; #IO_L11P_T1_SRCC_14 Sch=ck_io[8]
set_property -dict { PACKAGE_PIN M16   IOSTANDARD LVCMOS33 } [get_ports { selSign  }]; #IO_L10P_T1_D14_14 Sch=ck_io[9]
set_property -dict { PACKAGE_PIN V17   IOSTANDARD LVCMOS33 } [get_ports { Vld }]; #IO_L18N_T2_A11_D27_14 Sch=ck_io[10]
set_property -dict { PACKAGE_PIN U18   IOSTANDARD LVCMOS33 } [get_ports { selXY }]; #IO_L17N_T2_A13_D29_14 Sch=ck_io[11]
set_property -dict { PACKAGE_PIN R17   IOSTANDARD LVCMOS33 } [get_ports { En }]; #IO_L12N_T1_MRCC_14 Sch=ck_io[12]
set_property -dict { PACKAGE_PIN P17   IOSTANDARD LVCMOS33 } [get_ports { clk }]; #IO_L12P_T1_MRCC_14 Sch=ck_io[13]

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
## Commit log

2026-01-07 My Chip 25y1st NCO
2026-01-07 Rename NCO_PCB_1.png to images/NCO_PCB_1.png
2026-01-07 Rename architecture.png to images/architecture.png
